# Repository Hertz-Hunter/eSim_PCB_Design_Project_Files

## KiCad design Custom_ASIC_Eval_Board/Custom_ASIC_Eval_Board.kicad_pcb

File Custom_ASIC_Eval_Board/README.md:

# Custom ASIC Evaluation Board (Task 7 - Pratyush Kumar)

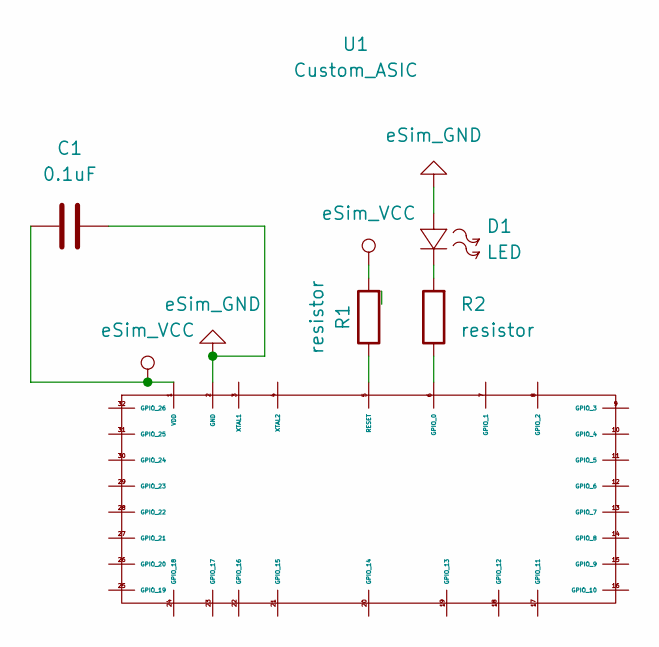
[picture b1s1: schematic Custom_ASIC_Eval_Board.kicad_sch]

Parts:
C1: 0.1uF; C_Disc_D5.0mm_W2.5mm_P2.50mm
D1: LED; LED_D5.0mm
R1, R2: resistor; R_Axial_DIN0207_L6.3mm_D2.5mm_P10.16mm_Horizontal
U1: Custom_ASIC; DIP-32_W15.24mm

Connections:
GND: C1.2, D1.1 (+), U1.2 (GND)
unnamed: D1.2 (-), R2.2
unnamed: R1.1, U1.5 (RESET)
unnamed: R2.1, U1.6 (GPIO_0)
VCC: C1.1, R1.2, U1.1 (VDD)

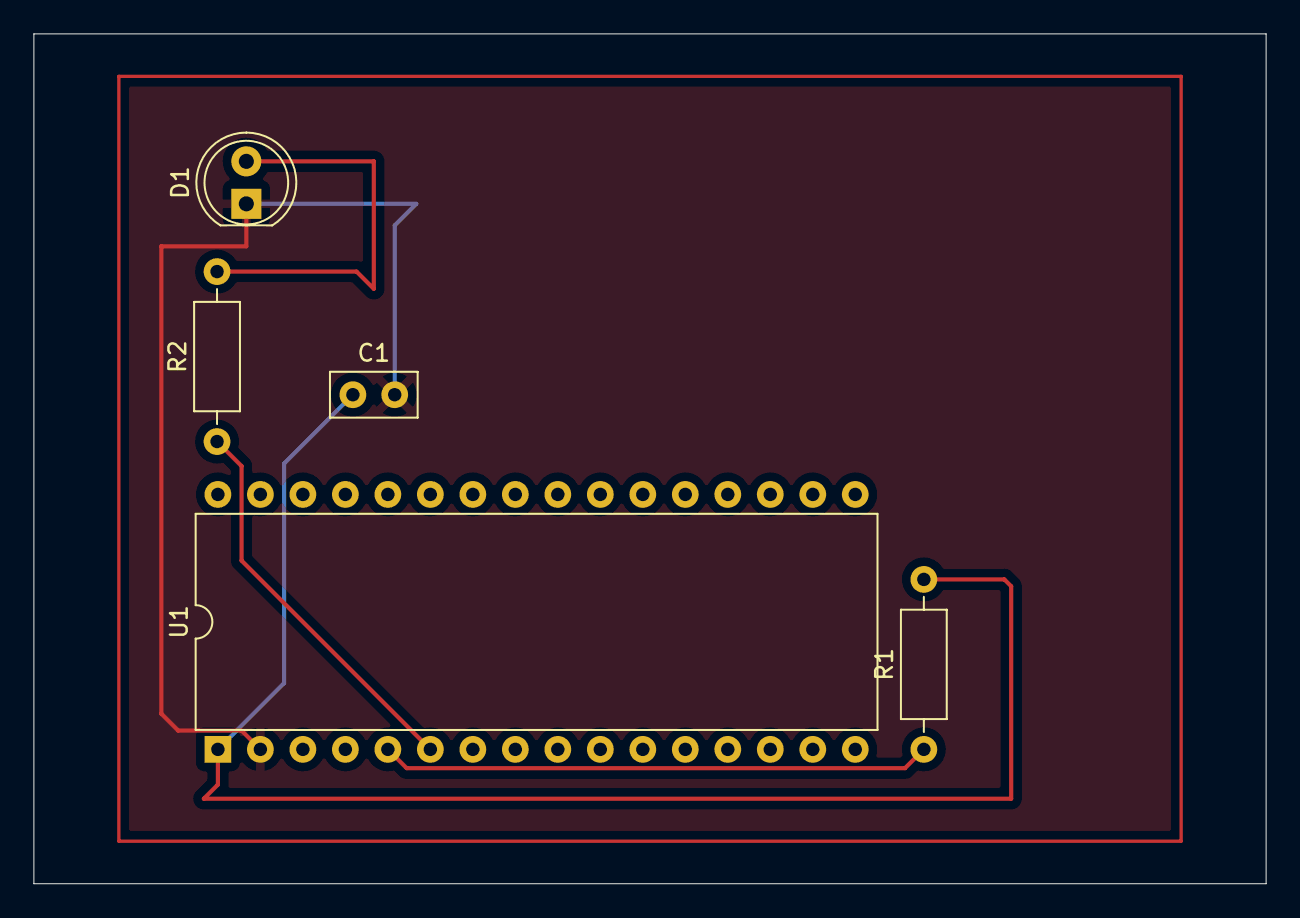
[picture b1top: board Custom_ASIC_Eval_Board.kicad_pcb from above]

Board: 2 copper layers, 73.7 x 50.8 mm, 5 parts (0 on the bottom side), 5 nets.
